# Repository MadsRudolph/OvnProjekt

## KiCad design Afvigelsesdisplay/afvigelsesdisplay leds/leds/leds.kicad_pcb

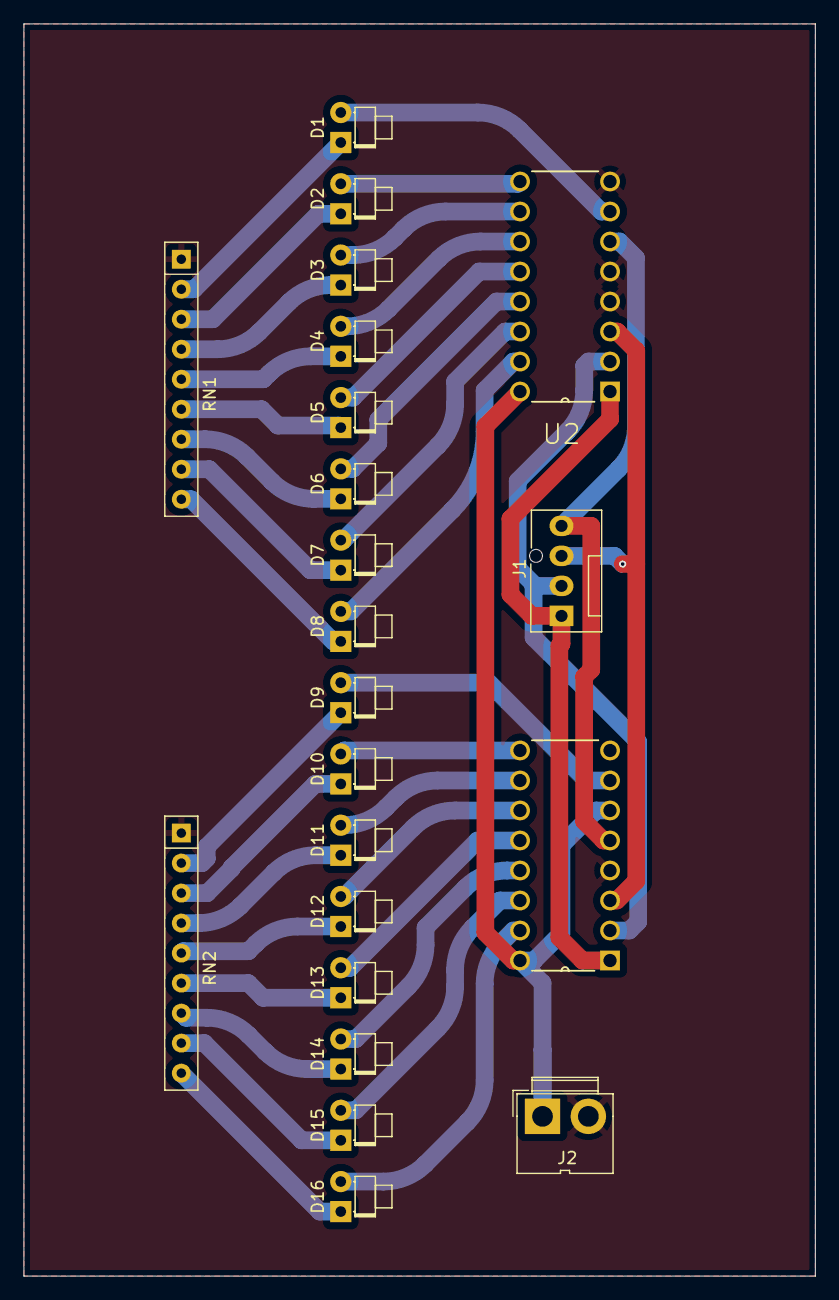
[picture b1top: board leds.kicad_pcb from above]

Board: 2 copper layers, 67.0 x 106.0 mm, 22 parts (0 on the bottom side), 38 nets.

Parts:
D1, D2, D3, D4, D5, D6, D7, D8, D9, D10, D11, D12, D13, D14, D15, D16: LED; LED_D1.8mm_W1.8mm_H2.4mm_Horizontal_O1.27mm_Z8.2mm
J1: Conn_01x04_Socket; FanPinHeader_1x04_P2.54mm_Vertical
J2: Conn_01x02_Pin; JWT_A3963_1x02_P3.96mm_Vertical
RN1, RN2: R_Network08; R_Array_SIP9
U2, U3: 74HC238N; DIP254P762X420-16

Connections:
GND: J2.2, RN1.1 (common), RN2.1 (common), U2.4 (~E1), U2.5 (~E2), U2.8 (GND), U3.4 (~E1), U3.8 (GND)
unnamed: D1.2 (A), U2.7 (Y7)
unnamed: D1.1 (K), RN1.2 (R1)
unnamed: D2.2 (A), U2.9 (Y6)
unnamed: D2.1 (K), RN1.3 (R2)
unnamed: D3.2 (A), U2.10 (Y5)
unnamed: D3.1 (K), RN1.4 (R3)
unnamed: D4.2 (A), U2.11 (Y4)
unnamed: D4.1 (K), RN1.5 (R4)
unnamed: D5.2 (A), U2.12 (Y3)
unnamed: D5.1 (K), RN1.6 (R5)
unnamed: D6.2 (A), U2.13 (Y2)
unnamed: D6.1 (K), RN1.7 (R6)
unnamed: D7.2 (A), U2.14 (Y1)
unnamed: D7.1 (K), RN1.8 (R7)
unnamed: D8.2 (A), U2.15 (Y0)
unnamed: D8.1 (K), RN1.9 (R8)
unnamed: D9.2 (A), U3.7 (Y7)
unnamed: D9.1 (K), RN2.2 (R1)
unnamed: D10.2 (A), U3.9 (Y6)
unnamed: D10.1 (K), RN2.3 (R2)
unnamed: D11.2 (A), U3.10 (Y5)
unnamed: D11.1 (K), RN2.4 (R3)
unnamed: D12.2 (A), U3.11 (Y4)
unnamed: D12.1 (K), RN2.5 (R4)
unnamed: D13.2 (A), U3.12 (Y3)
unnamed: D13.1 (K), RN2.6 (R5)
unnamed: D14.2 (A), U3.13 (Y2)
unnamed: D14.1 (K), RN2.7 (R6)
unnamed: D15.2 (A), U3.14 (Y1)
unnamed: D15.1 (K), RN2.8 (R7)
unnamed: D16.2 (A), U3.15 (Y0)
unnamed: D16.1 (K), RN2.9 (R8)
unnamed: J1.1, U2.1 (A0), U3.1 (A0)
unnamed: J1.2, U2.2 (A1), U3.2 (A1)
unnamed: J1.3, U2.3 (A2), U3.3 (A2)
unnamed: J1.4, U2.6 (E3), U3.5 (~E2)
VCC: J2.1, U2.16 (VCC), U3.6 (E3), U3.16 (VCC)

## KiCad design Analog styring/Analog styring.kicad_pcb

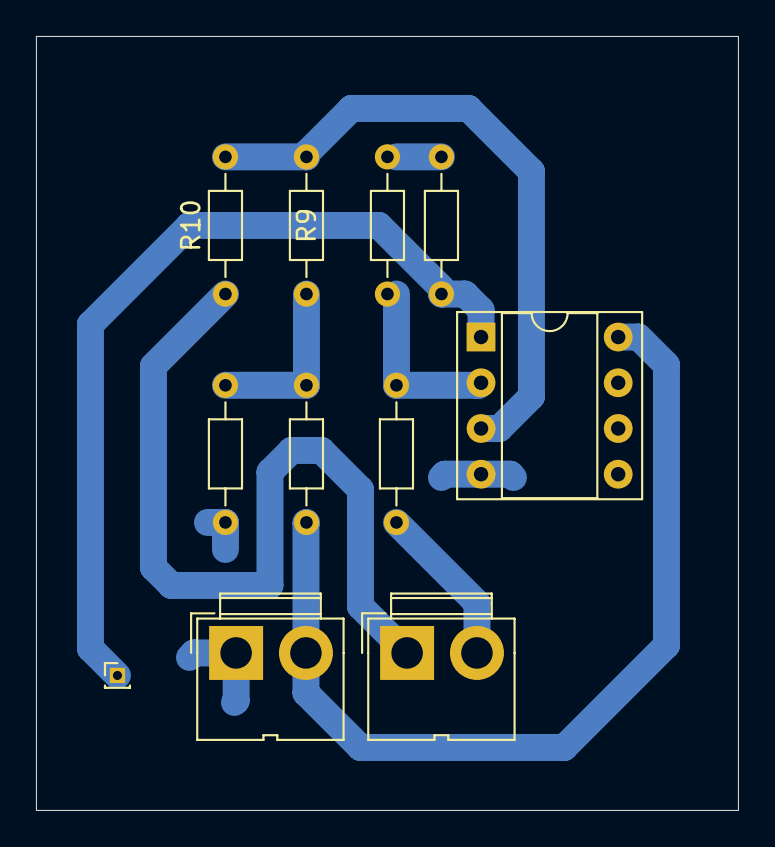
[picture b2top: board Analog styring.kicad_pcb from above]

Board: 2 copper layers, 39.0 x 43.0 mm, 11 parts (0 on the bottom side), 9 nets.

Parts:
5V_in1: 5V_in; JWT_A3963_1x02_P3.96mm_Vertical
11.5K1: R; R_Axial_DIN0204_L3.6mm_D1.6mm_P7.62mm_Horizontal
Afv_display1: Conn_01x01_Pin; PinHeader_1x01_P1.00mm_Vertical
Input_LM35_Spv1: Conn_01x02_Pin; JWT_A3963_1x02_P3.96mm_Vertical
R5, R6: 11.5K; R_Axial_DIN0204_L3.6mm_D1.6mm_P7.62mm_Horizontal
R7, R9: 301K; R_Axial_DIN0204_L3.6mm_D1.6mm_P7.62mm_Horizontal
R8, R10: 10K; R_Axial_DIN0204_L3.6mm_D1.6mm_P7.62mm_Horizontal
U1: MCP6002-xMC; DIP-8_W7.62mm_Socket

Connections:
+5V: 5V_in1.2, R5.2, U1.8 (V+)
Afv_displ_adc: 11.5K1.2, Afv_display1.1, U1.1
GND: 5V_in1.1, R6.2, U1.4 (V-)
LM35_out: Input_LM35_Spv1.1, R10.1
unnamed: 11.5K1.1, R7.2
unnamed: R5.1, R6.1, R9.1
unnamed: R9.2, R10.2, U1.3 (+)
unnamed: R7.1, R8.2, U1.2 (-)
Sp_v: Input_LM35_Spv1.2, R8.1

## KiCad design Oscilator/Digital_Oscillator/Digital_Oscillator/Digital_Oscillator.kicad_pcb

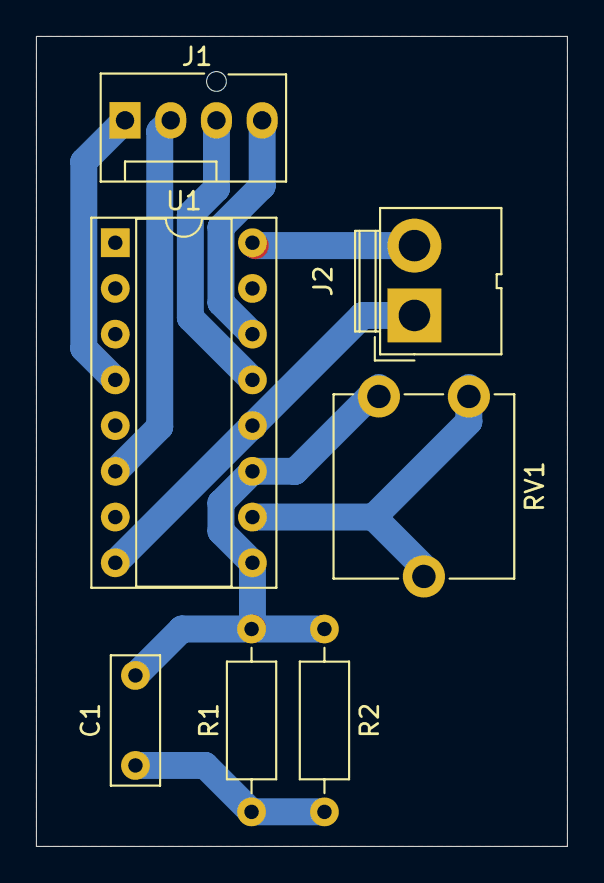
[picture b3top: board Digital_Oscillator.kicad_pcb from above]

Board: 2 copper layers, 29.5 x 45.0 mm, 7 parts (0 on the bottom side), 9 nets.

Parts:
C1: 100 nF; C_Disc_D7.0mm_W2.5mm_P5.00mm
J1: Conn_01x04_Socket; FanPinHeader_1x04_P2.54mm_Vertical
J2: Conn_01x02_Socket; JWT_A3963_1x02_P3.96mm_Vertical
R1: R; R_Axial_DIN0207_L6.3mm_D2.5mm_P10.16mm_Horizontal
R2: 123K6; R_Axial_DIN0207_L6.3mm_D2.5mm_P10.16mm_Horizontal
RV1: R_Potentiometer_Small; Potentiometer_ACP_CA9-V10_Vertical
U1: 74HC4060; DIP-16_W7.62mm_Socket

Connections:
GND: J2.1, U1.8 (VSS), U1.12 (CLR)
unnamed: C1.1, R1.1, R2.1
unnamed: J1.1, U1.4 (Q6)
unnamed: J1.2, U1.6 (Q7)
unnamed: J1.3, U1.13 (Q9)
unnamed: J1.4, U1.14 (Q8)
unnamed: C1.2, R1.2, R2.2, RV1.1, U1.9 (~Φ0), U1.11 (~Φ1)
unnamed: RV1.2, RV1.3, U1.10 (Φ0)
VCC: J2.2, U1.16 (VDD)

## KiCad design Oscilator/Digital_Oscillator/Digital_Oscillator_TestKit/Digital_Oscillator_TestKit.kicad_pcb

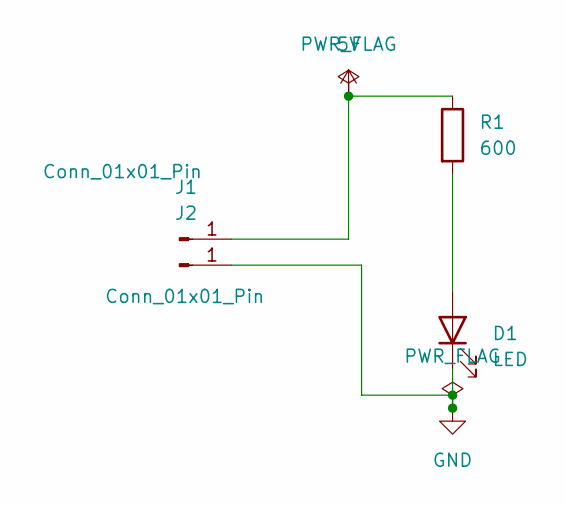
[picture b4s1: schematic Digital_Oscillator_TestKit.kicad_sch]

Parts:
D1: LED; LED_D1.8mm_W1.8mm_H2.4mm_Horizontal_O6.35mm_Z4.9mm
J1, J2: Conn_01x01_Pin; Pin_D1.0mm_L10.0mm
R1: 600; R_Axial_DIN0204_L3.6mm_D1.6mm_P7.62mm_Horizontal

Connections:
5V: J1.1, R1.1
GND: D1.1 (K), J2.1
unnamed: D1.2 (A), R1.2

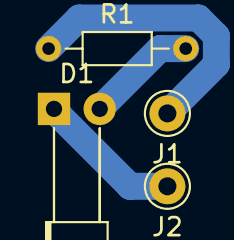
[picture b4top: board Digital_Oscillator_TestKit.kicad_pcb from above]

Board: 2 copper layers, 4 parts (0 on the bottom side), 3 nets.
